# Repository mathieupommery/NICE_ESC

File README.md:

# NICE ESC

**A two-board, high-current three-phase inverter for BLDC/PMSM motor control and bidirectional power conversion.**

## Capabilities and key components

- **4S–16S Li-ion design range** or **84 V / 20S variant** with higher-voltage MOSFETs.
- **200 A peak phase-current design target**, with double-pulse switching tests extended to approximately **328 A** at a 40 V bus. Need a good cooling and test in continuous current.
- Hardware for **six-step control, FOC, Hall-based position feedback and active rectification**, depending on the firmware.
- all TOLT top side cooled mosfet to keep the case cost low we only have to cool down one isde of the inverter, also no need for aluminium or copper pcb.

| Function | Hardware |
|---|---|
| Controller | STM32G431CBU, complementary PWM and synchronized ADC acquisition |
| Power switches | 12 × IAUS300N10S5N015T, with two MOSFETs in parallel per switch |
| Gate drive | UCC27301A half-bridge drivers, bootstrap circuits and approximately 11 V gate supply |
| Current sensing | Shunts and INA241 amplifiers located on the power PCB |
| Signal conditioning | Switchable RC filters for current and voltage measurements |
| Auxiliary rails | LM5169 bus-to-11 V buck, LMR51625 11-to-5 V buck, separate 3.3 V digital and analog rails |
| Interconnects | M5 battery/phase terminals and locking JST-GH signal connectors |
| PCB stack-up | Four copper layers on the control board; two on the power board |

The published switching measurements were made at approximately **40 V**, not at the maximum intended battery voltage.

## V2 architecture

The two boards share a common electrical reference. Gate drivers, gate components and current amplifiers are kept close to the power devices, so the board-to-board connections carry logic-level PWM and amplified measurements rather than long gate loops or raw shunt signals.An effort has been put on the esd and overvoltage protection, each voltage rail has it's on esd protection as well as each connection.

## Assembly and mechanical integration

The control PCB sits above the power PCB. Top-side-cooled TOLT MOSFETs are mounted on the underside of the power board, providing access to their cooling surfaces. STEP models of both boards and the enclosure are included.

## TOLT MOSFET options

The baseline device is the **IAUS300N10S5N015T**, an OptiMOS 5 100 V TOLT MOSFET. Higher-voltage OptiMOS 6 devices offer a useful trade-off between voltage headroom and on-resistance:

| Device | Technology | VDS rating | Maximum RDS(on), VGS = 10 V | Role |
|---|---|---:|---:|---|
| [IAUS300N10S5N015T](https://www.infineon.com/part/IAUS300N10S5N015T) | OptiMOS 5 | 100 V | 1.5 mΩ | Baseline build |
| [IPTC017N12NM6](https://www.infineon.com/part/IPTC017N12NM6) | OptiMOS 6 | 120 V | 1.7 mΩ | Higher-voltage candidate |
| [IPTC020N13NM6](https://www.infineon.com/part/IPTC020N13NM6) | OptiMOS 6 | 135 V | 2.0 mΩ | Additional voltage headroom |

The 120 V option adds only 0.2 mΩ relative to the baseline.Also infineon will eventually create new optimos 8 mosfet in tolt wich can improve the choice.

## Double-pulse testing

A double-pulse test first builds current in an air-core inductor, then captures turn-off and the subsequent turn-on under load. The measurements below were taken at approximately **40 V bus voltage and 200 A inductor current**, using an approximately **8 µH** air-core load, all measurment are donne at 2.5Gsamples/s on tektronix MDO3034 scope with 1GHz probes.

At 200 A, the recorded drain-source peaks remain around **60 V on a 40 V bus**, leaving substantial headroom below the baseline MOSFET's 100 V rating. The extracted VDS transition times are approximately **101 ns at turn-on** and **33 ns at turn-off**. These are voltage-edge durations, not complete gate-command delays.

The test campaign was also pushed to approximately **328 A**, the current acquisition range limit, without a notable increase in the observed VDS peaks. The plots shown here are the **200 A acquisition**. These short-pulse results are encouraging for the commutation layout; sustained phase-current capability still depends on thermal validation.

The measured current is the inductor current, so the captures are used to assess overshoot and ringing rather than to claim precise Eon/Eoff measurements. [Raw acquisitions and the viewer](DOC_AND_SIMULATION/DPT_200A/) and the [LTspice test circuit](DOC_AND_SIMULATION/LTSPICE_SIMULATION_DPT/) are included.

## DC-link decoupling

The DC link combines bulk energy storage with local, low-inductance ceramic decoupling:

| Capacitor bank | Selection | Purpose |
|---|---|---|
| Bulk electrolytics | **4 × 820 µF / 100 V = 3280 µF** | Reduce the lower-frequency DC-link ripple and supply transient energy |
| Local MLCCs | **18 × 4.7 µF / 100 V, 2220 = 84.6 µF nominal** | Supply fast switching-current loops close to the half-bridges and limit parasitic-inductance overshoot |

For a first-order capacitive-ripple estimate, `ΔVpp ≈ Iphase,peak / (4 × fPWM × Cbulk)`. At **200 A and 20 kHz**, a 2 V ripple target gives **1250 µF minimum**; the selected 3280 µF gives approximately **0.76 V calculated capacitive ripple**. Actual ripple also depends on ESR/ESL, RMS current and temperature. The MLCC total is nominal: effective capacitance falls with DC bias. Placement and short commutation loops matter alongside the capacitance value.

## Repository

| Directory | Contents |
|---|---|
| [Control PCB](HARDWARE/V2/CONTROL_BOARD_V2/) | KiCad project, schematics, layout and local libraries |
| [Power PCB](HARDWARE/V2/POWER_BOARD_V2/) | KiCad project, schematics, layout and local libraries |
| [Board STEP models](HARDWARE/V2/3D/) | Mechanical board assemblies |
| [Enclosure](HARDWARE/INVERTER_CASE_3D/) | Top and bottom STEP models |
| [Documentation and simulation](DOC_AND_SIMULATION/) | DPT data, LTspice files and project media |

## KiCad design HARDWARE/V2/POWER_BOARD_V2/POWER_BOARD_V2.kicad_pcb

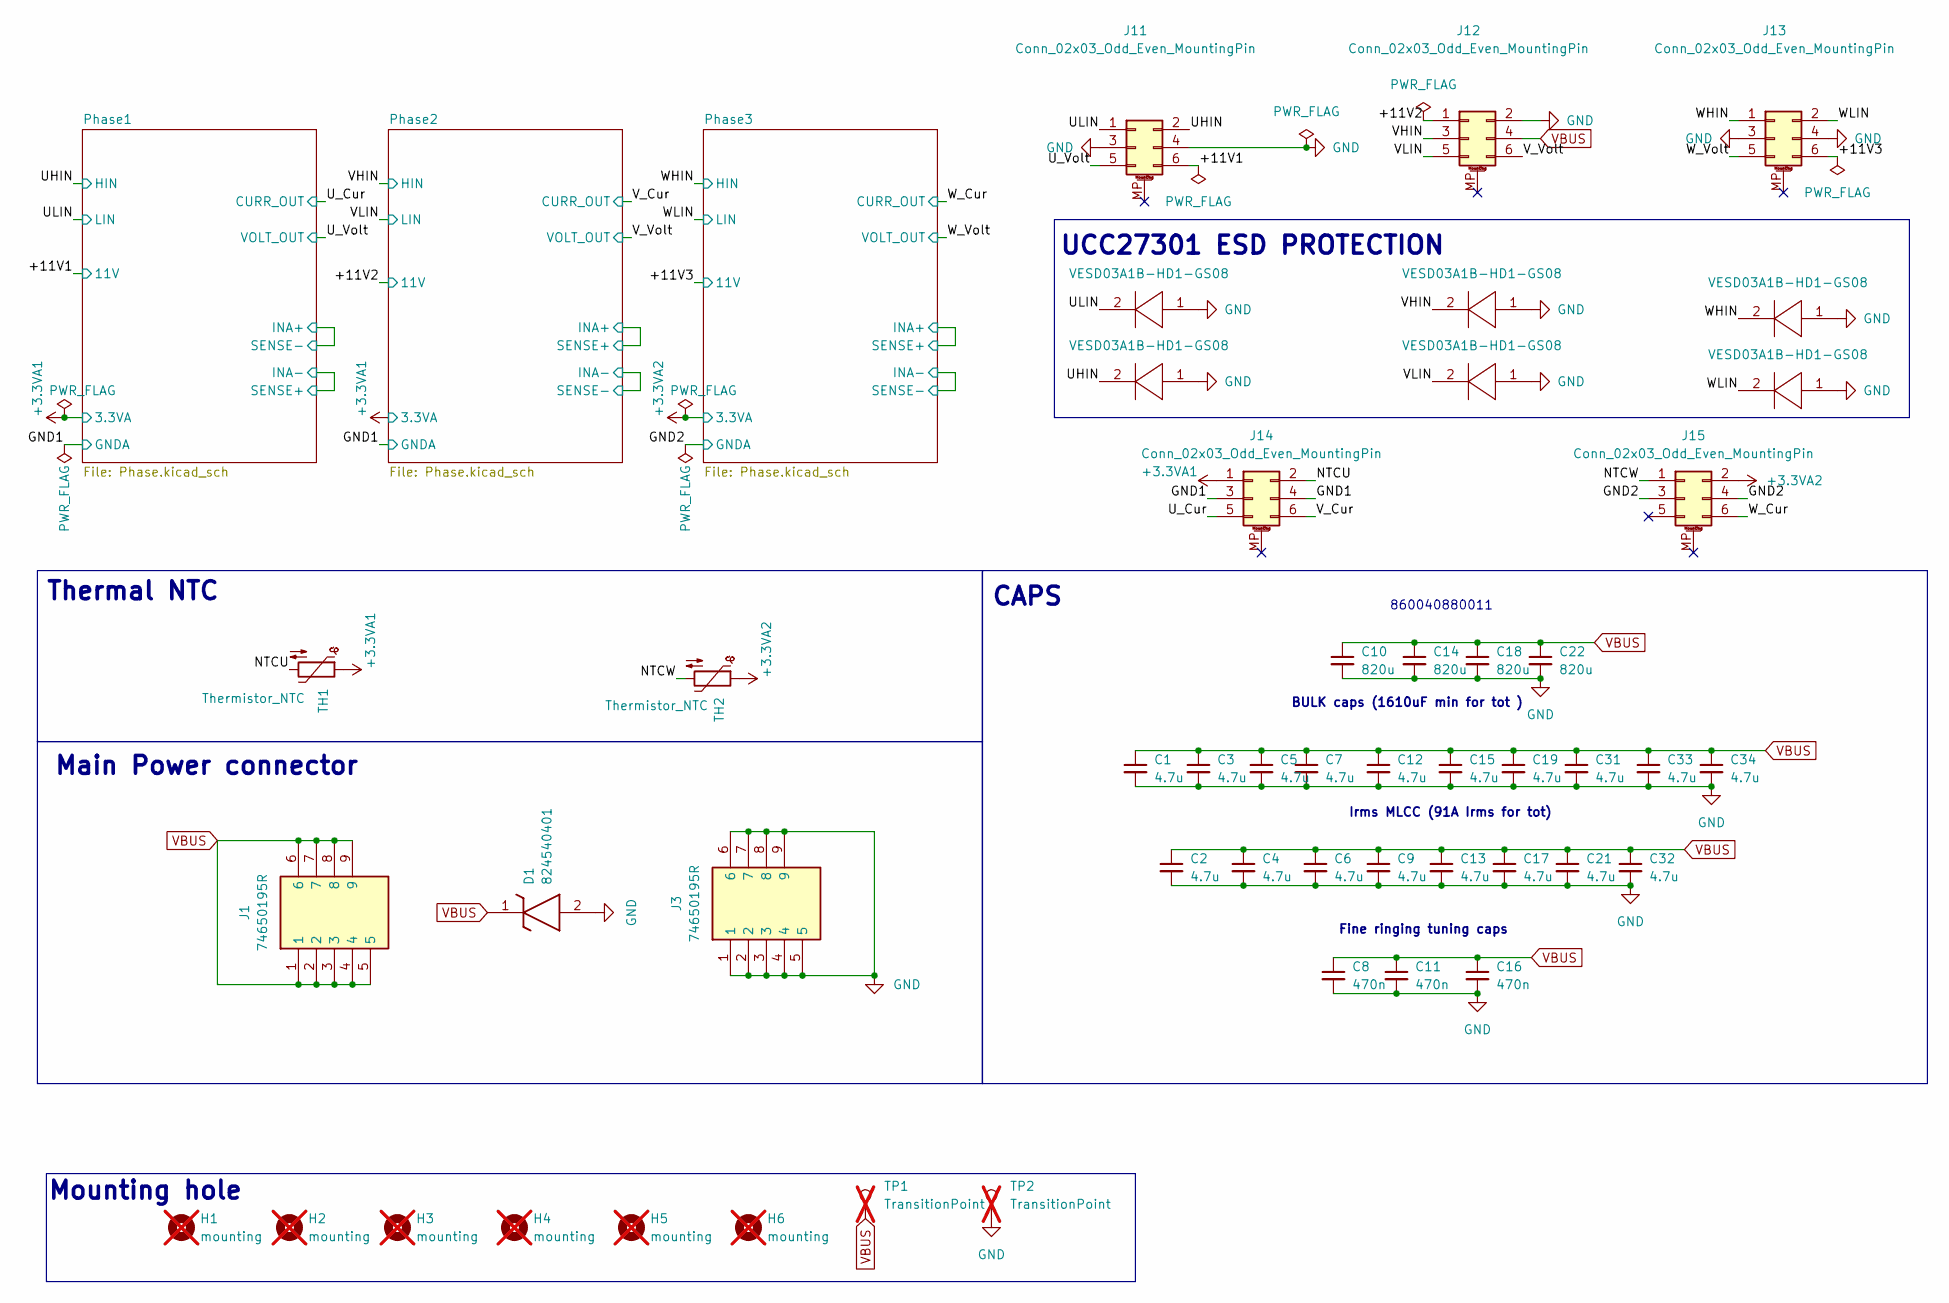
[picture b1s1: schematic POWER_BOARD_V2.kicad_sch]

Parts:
C1, C2, C3, C4, C5, C6, C7, C9, C12, C13, C15, C17, C19, C21, C31, C32, C33, C34: 4.7u; C_2220_5750Metric
C8, C11, C16: 470n; C_1206_3216Metric
C10, C14, C18, C22: 820u; CAPPRD750W82D1800H3300
D1: 824540401; DIOM7959X250N; Manufacturer_Part_Number 824540401; Mouser Part Number 710-824540401
D19, D20, D21, D22, D23, D24: VESD03A1B-HD1-GS08; VCUT0714AHD1G308; Manufacturer_Part_Number VESD03A1B-HD1-GS08; Mouser Part Number 78-VESD03A1B-HD1
H1, H2, H3, H4, H5, H6: mounting; MountingHole_3.2mm_M3_ISO7380; not fitted
J1, J3: 74650195R; 74651194R; Manufacturer_Part_Number 74650195R; Mouser Part Number 710-74650195R
J11, J12, J13, J14, J15: Conn_02x03_Odd_Even_MountingPin; pinheader_02x03_Custom
TH1, TH2: Thermistor_NTC; R_0402_1005Metric
TP1, TP2: TransitionPoint; bighole2mm; not fitted

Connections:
+3.3VA1: J14.1, TH1.1; also elsewhere on the board
+3.3VA2: J15.2, TH2.1; also elsewhere on the board
/+11V1: J11.6; also elsewhere on the board
/+11V2: J12.1; also elsewhere on the board
/+11V3: J13.6; also elsewhere on the board
/GND1: J14.3, J14.4; also elsewhere on the board
/GND2: J15.3, J15.4; also elsewhere on the board
/NTCU: J14.2, TH1.2
/NTCW: J15.1, TH2.2
/UHIN: D20.2, D20.4 (K_2), J11.2; also elsewhere on the board
/ULIN: D19.2, D19.4 (K_2), J11.1; also elsewhere on the board
/U_Cur: J14.5; also elsewhere on the board
/U_Volt: J11.5; also elsewhere on the board
/VHIN: D21.2, D21.4 (K_2), J12.3; also elsewhere on the board
/VLIN: D22.2, D22.4 (K_2), J12.5; also elsewhere on the board
/V_Cur: J14.6; also elsewhere on the board
/V_Volt: J12.6; also elsewhere on the board
/WHIN: D23.2, D23.4 (K_2), J13.1; also elsewhere on the board
/WLIN: D24.2, D24.4 (K_2), J13.2; also elsewhere on the board
/W_Cur: J15.6; also elsewhere on the board
/W_Volt: J13.5; also elsewhere on the board
GND: C1.2, C2.2, C3.2, C4.2, C5.2, C6.2, C7.2, C8.2, C9.2, C10.2, C11.2, C12.2, C13.2, C14.2, C15.2, C16.2, C17.2, C18.2, C19.2, C21.2, C22.2, C31.2, C32.2, C33.2, C34.2, D1.2 (A), D19.1, D19.3 (A_2), D20.1, D20.3 (A_2), D21.1, D21.3 (A_2), D22.1, D22.3 (A_2), D23.1, D23.3 (A_2), D24.1, D24.3 (A_2), J3.1, J3.2, J3.3, J3.4, J3.5, J3.6, J3.7, J3.8, J3.9, J11.3, J11.4, J12.2, J13.3, J13.4, TP2.1 (1_1); also elsewhere on the board
VBUS: C1.1, C2.1, C3.1, C4.1, C5.1, C6.1, C7.1, C8.1, C9.1, C10.1, C11.1, C12.1, C13.1, C14.1, C15.1, C16.1, C17.1, C18.1, C19.1, C21.1, C22.1, C31.1, C32.1, C33.1, C34.1, D1.1 (K), J1.1, J1.2, J1.3, J1.4, J1.5, J1.6, J1.7, J1.8, J1.9, J12.4, TP1.1 (1_1); also elsewhere on the board

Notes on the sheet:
CAPS
Main Power connector
Thermal NTC
Mounting hole
Irms MLCC (91A Irms for tot)
Fine ringing tuning caps
BULK caps (1610uF min for tot )
860040880011
UCC27301 ESD PROTECTION

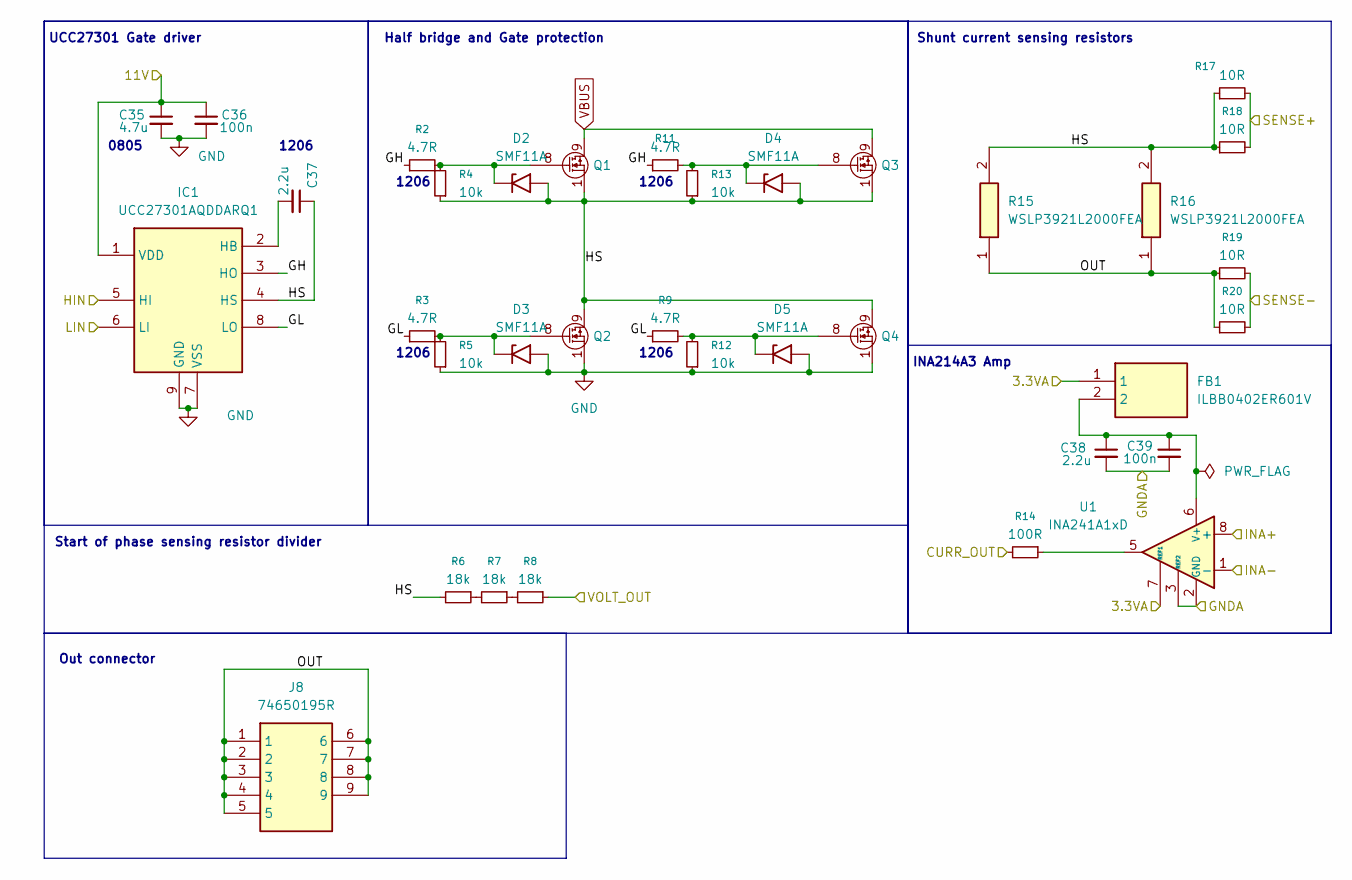
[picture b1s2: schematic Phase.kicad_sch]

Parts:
C35: 4.7u; C_0805_2012Metric
C36, C39: 100n; C_0402_1005Metric
C37: 2.2u; C_1206_3216Metric
C38: 2.2u; C_0402_1005Metric
D2, D3, D4, D5: SMF11A; SMF_Custom
FB1: ILBB0402ER601V; BEADC1005X60N; Manufacturer_Part_Number ILBB0402ER601V; Mouser Part Number 70-ILBB0402ER601V
IC1: UCC27301AQDDARQ1; SOIC127P600X170-9N; Manufacturer_Part_Number UCC27301AQDDARQ1; Mouser Part Number 595-UCC27301AQDDARQ1
J8: 74650195R; 74651194R; Manufacturer_Part_Number 74650195R; Mouser Part Number 710-74650195R
Q1, Q2, Q3, Q4: IAUS300N10S5N015TATMA1; SOP120P1500X235-16N; Manufacturer_Part_Number IAUS300N10S5N015TATMA1; Mouser Part Number 726-US300N10S5N015T1
R2, R3, R9, R11: 4.7R; R_1206_3216Metric
R4, R5, R12, R13: 10k; R_0402_1005Metric
R6, R7, R8: 18k; R_0402_1005Metric
R14: 100R; R_0402_1005Metric
R15, R16: WSLP3921L2000FEA; RESC10052X69N; Manufacturer_Part_Number WSLP3921L2000FEA; Mouser Part Number 71-WSLP3921L2000FEA
R17, R18, R19, R20: 10R; R_0402_1005Metric
U1: INA241A1xD; SOIC-8_3.9x4.9mm_P1.27mm

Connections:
+3.3VA1: FB1.1, U1.7 (REF1); also elsewhere on the board
/+11V1: C35.1, C36.1, IC1.1 (VDD); also elsewhere on the board
/GND1: C38.2, C39.2, U1.2 (GND), U1.3 (REF2), U1.4 (GND); also elsewhere on the board
/Phase1/GH: IC1.3 (HO), R2.1, R11.1
/Phase1/GL: IC1.8 (LO), R3.1, R9.1
/Phase1/HS: C37.1, D2.2 (A2), D4.2 (A2), IC1.4 (HS), Q1.1, Q1.2 (S_2), Q1.3 (S_3), Q1.4 (S_4), Q1.5 (S_5), Q1.6 (S_6), Q1.7 (S_7), Q2.9, Q2.10 (D_2), Q2.11 (D_3), Q2.12 (D_4), Q2.13 (D_5), Q2.14 (D_6), Q2.15 (D_7), Q2.16 (D_8), Q3.1, Q3.2 (S_2), Q3.3 (S_3), Q3.4 (S_4), Q3.5 (S_5), Q3.6 (S_6), Q3.7 (S_7), Q4.9, Q4.10 (D_2), Q4.11 (D_3), Q4.12 (D_4), Q4.13 (D_5), Q4.14 (D_6), Q4.15 (D_7), Q4.16 (D_8), R4.1, R6.2, R13.1, R15.2, R16.2, R17.1, R18.1
/Phase1/INA+: R19.2, R20.2, U1.8 (+)
/Phase1/INA-: R17.2, R18.2, U1.1 (-)
/Phase1/OUT: J8.1, J8.2, J8.3, J8.4, J8.5, J8.6, J8.7, J8.8, J8.9, R15.1, R16.1, R19.1, R20.1
/UHIN: IC1.5 (HI); also elsewhere on the board
/ULIN: IC1.6 (LI); also elsewhere on the board
/U_Cur: R14.2; also elsewhere on the board
/U_Volt: R8.1; also elsewhere on the board
GND: C35.2, C36.2, D3.2 (A2), D5.2 (A2), IC1.7 (VSS), IC1.9 (GND), Q2.1, Q2.2 (S_2), Q2.3 (S_3), Q2.4 (S_4), Q2.5 (S_5), Q2.6 (S_6), Q2.7 (S_7), Q4.1, Q4.2 (S_2), Q4.3 (S_3), Q4.4 (S_4), Q4.5 (S_5), Q4.6 (S_6), Q4.7 (S_7), R5.1, R12.1; also elsewhere on the board
unnamed: D2.1 (A1), Q1.8, R2.2, R4.2
unnamed: D3.1 (A1), Q2.8, R3.2, R5.2
unnamed: D4.1 (A1), Q3.8, R11.2, R13.2
unnamed: D5.1 (A1), Q4.8, R9.2, R12.2
unnamed: C37.2, IC1.2 (HB)
unnamed: R6.1, R7.2
unnamed: R7.1, R8.2
unnamed: R14.1, U1.5
unnamed: C38.1, C39.1, FB1.2, U1.6 (V+)
VBUS: Q1.9, Q1.10 (D_2), Q1.11 (D_3), Q1.12 (D_4), Q1.13 (D_5), Q1.14 (D_6), Q1.15 (D_7), Q1.16 (D_8), Q3.9, Q3.10 (D_2), Q3.11 (D_3), Q3.12 (D_4), Q3.13 (D_5), Q3.14 (D_6), Q3.15 (D_7), Q3.16 (D_8); also elsewhere on the board

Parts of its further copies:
C40, C45: 4.7u; C_0805_2012Metric
C41, C44, C46, C49: 100n; C_0402_1005Metric
C42, C47: 2.2u; C_1206_3216Metric
C43, C48: 2.2u; C_0402_1005Metric
D6, D7, D8, D9, D10, D11, D12, D13: SMF11A; SMF_Custom
FB2, FB3: ILBB0402ER601V; BEADC1005X60N; Manufacturer_Part_Number ILBB0402ER601V; Mouser Part Number 70-ILBB0402ER601V
IC2, IC3: UCC27301AQDDARQ1; SOIC127P600X170-9N; Manufacturer_Part_Number UCC27301AQDDARQ1; Mouser Part Number 595-UCC27301AQDDARQ1
J9, J10: 74650195R; 74651194R; Manufacturer_Part_Number 74650195R; Mouser Part Number 710-74650195R
Q5, Q6, Q7, Q8, Q9, Q10, Q11, Q12: IAUS300N10S5N015TATMA1; SOP120P1500X235-16N; Manufacturer_Part_Number IAUS300N10S5N015TATMA1; Mouser Part Number 726-US300N10S5N015T1
R21, R22, R28, R30, R40, R41, R47, R49: 4.7R; R_1206_3216Metric
R23, R24, R31, R32, R42, R43, R50, R51: 10k; R_0402_1005Metric
R25, R26, R27, R44, R45, R46: 18k; R_0402_1005Metric
R33, R52: 100R; R_0402_1005Metric
R34, R35, R53, R54: WSLP3921L2000FEA; RESC10052X69N; Manufacturer_Part_Number WSLP3921L2000FEA; Mouser Part Number 71-WSLP3921L2000FEA
R36, R37, R38, R39, R55, R56, R57, R58: 10R; R_0402_1005Metric
U2, U3: INA241A1xD; SOIC-8_3.9x4.9mm_P1.27mm

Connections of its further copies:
+3.3VA1: FB2.1, U2.7 (REF1); also elsewhere on the board
+3.3VA2: FB3.1, U3.7 (REF1); also elsewhere on the board
/+11V2: C40.1, C41.1, IC2.1 (VDD); also elsewhere on the board
/+11V3: C45.1, C46.1, IC3.1 (VDD); also elsewhere on the board
/GND1: C43.2, C44.2, U2.2 (GND), U2.3 (REF2), U2.4 (GND); also elsewhere on the board
/GND2: C48.2, C49.2, U3.2 (GND), U3.3 (REF2), U3.4 (GND); also elsewhere on the board
/Phase2/GH: IC2.3 (HO), R21.1, R30.1
/Phase2/GL: IC2.8 (LO), R22.1, R28.1
/Phase2/HS: C42.1, D6.2 (A2), D8.2 (A2), IC2.4 (HS), Q5.1, Q5.2 (S_2), Q5.3 (S_3), Q5.4 (S_4), Q5.5 (S_5), Q5.6 (S_6), Q5.7 (S_7), Q6.9, Q6.10 (D_2), Q6.11 (D_3), Q6.12 (D_4), Q6.13 (D_5), Q6.14 (D_6), Q6.15 (D_7), Q6.16 (D_8), Q7.1, Q7.2 (S_2), Q7.3 (S_3), Q7.4 (S_4), Q7.5 (S_5), Q7.6 (S_6), Q7.7 (S_7), Q8.9, Q8.10 (D_2), Q8.11 (D_3), Q8.12 (D_4), Q8.13 (D_5), Q8.14 (D_6), Q8.15 (D_7), Q8.16 (D_8), R23.1, R25.2, R32.1, R34.2, R35.2, R36.1, R37.1
/Phase2/INA+: R36.2, R37.2, U2.8 (+)
/Phase2/INA-: R38.2, R39.2, U2.1 (-)
/Phase2/OUT: J9.1, J9.2, J9.3, J9.4, J9.5, J9.6, J9.7, J9.8, J9.9, R34.1, R35.1, R38.1, R39.1
/Phase3/GH: IC3.3 (HO), R40.1, R49.1
/Phase3/GL: IC3.8 (LO), R41.1, R47.1
/Phase3/HS: C47.1, D10.2 (A2), D12.2 (A2), IC3.4 (HS), Q9.1, Q9.2 (S_2), Q9.3 (S_3), Q9.4 (S_4), Q9.5 (S_5), Q9.6 (S_6), Q9.7 (S_7), Q10.9, Q10.10 (D_2), Q10.11 (D_3), Q10.12 (D_4), Q10.13 (D_5), Q10.14 (D_6), Q10.15 (D_7), Q10.16 (D_8), Q11.1, Q11.2 (S_2), Q11.3 (S_3), Q11.4 (S_4), Q11.5 (S_5), Q11.6 (S_6), Q11.7 (S_7), Q12.9, Q12.10 (D_2), Q12.11 (D_3), Q12.12 (D_4), Q12.13 (D_5), Q12.14 (D_6), Q12.15 (D_7), Q12.16 (D_8), R42.1, R44.2, R51.1, R53.2, R54.2, R55.1, R56.1
/Phase3/INA+: R55.2, R56.2, U3.8 (+)
/Phase3/INA-: R57.2, R58.2, U3.1 (-)
/Phase3/OUT: J10.1, J10.2, J10.3, J10.4, J10.5, J10.6, J10.7, J10.8, J10.9, R53.1, R54.1, R57.1, R58.1
/VHIN: IC2.5 (HI); also elsewhere on the board
/VLIN: IC2.6 (LI); also elsewhere on the board
/V_Cur: R33.2; also elsewhere on the board
/V_Volt: R27.1; also elsewhere on the board
/WHIN: IC3.5 (HI); also elsewhere on the board
/WLIN: IC3.6 (LI); also elsewhere on the board
/W_Cur: R52.2; also elsewhere on the board
/W_Volt: R46.1; also elsewhere on the board
GND: C40.2, C41.2, C45.2, C46.2, D7.2 (A2), D9.2 (A2), D11.2 (A2), D13.2 (A2), IC2.7 (VSS), IC2.9 (GND), IC3.7 (VSS), IC3.9 (GND), Q6.1, Q6.2 (S_2), Q6.3 (S_3), Q6.4 (S_4), Q6.5 (S_5), Q6.6 (S_6), Q6.7 (S_7), Q8.1, Q8.2 (S_2), Q8.3 (S_3), Q8.4 (S_4), Q8.5 (S_5), Q8.6 (S_6), Q8.7 (S_7), Q10.1, Q10.2 (S_2), Q10.3 (S_3), Q10.4 (S_4), Q10.5 (S_5), Q10.6 (S_6), Q10.7 (S_7), Q12.1, Q12.2 (S_2), Q12.3 (S_3), Q12.4 (S_4), Q12.5 (S_5), Q12.6 (S_6), Q12.7 (S_7), R24.1, R31.1, R43.1, R50.1; also elsewhere on the board
unnamed: D6.1 (A1), Q5.8, R21.2, R23.2
unnamed: D7.1 (A1), Q6.8, R22.2, R24.2
unnamed: D8.1 (A1), Q7.8, R30.2, R32.2
unnamed: D9.1 (A1), Q8.8, R28.2, R31.2
unnamed: D10.1 (A1), Q9.8, R40.2, R42.2
unnamed: D11.1 (A1), Q10.8, R41.2, R43.2
unnamed: D12.1 (A1), Q11.8, R49.2, R51.2
unnamed: D13.1 (A1), Q12.8, R47.2, R50.2
unnamed: C42.2, IC2.2 (HB)
unnamed: C47.2, IC3.2 (HB)
unnamed: R25.1, R26.2
unnamed: R26.1, R27.2
unnamed: R33.1, U2.5
unnamed: R44.1, R45.2
unnamed: R45.1, R46.2
unnamed: R52.1, U3.5
unnamed: C43.1, C44.1, FB2.2, U2.6 (V+)
unnamed: C48.1, C49.1, FB3.2, U3.6 (V+)
VBUS: Q5.9, Q5.10 (D_2), Q5.11 (D_3), Q5.12 (D_4), Q5.13 (D_5), Q5.14 (D_6), Q5.15 (D_7), Q5.16 (D_8), Q7.9, Q7.10 (D_2), Q7.11 (D_3), Q7.12 (D_4), Q7.13 (D_5), Q7.14 (D_6), Q7.15 (D_7), Q7.16 (D_8), Q9.9, Q9.10 (D_2), Q9.11 (D_3), Q9.12 (D_4), Q9.13 (D_5), Q9.14 (D_6), Q9.15 (D_7), Q9.16 (D_8), Q11.9, Q11.10 (D_2), Q11.11 (D_3), Q11.12 (D_4), Q11.13 (D_5), Q11.14 (D_6), Q11.15 (D_7), Q11.16 (D_8); also elsewhere on the board

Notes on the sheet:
1206
Shunt current sensing resistors
0805
Half bridge and Gate protection
Start of phase sensing resistor divider
UCC27301 Gate driver
Out connector
INA214A3 Amp

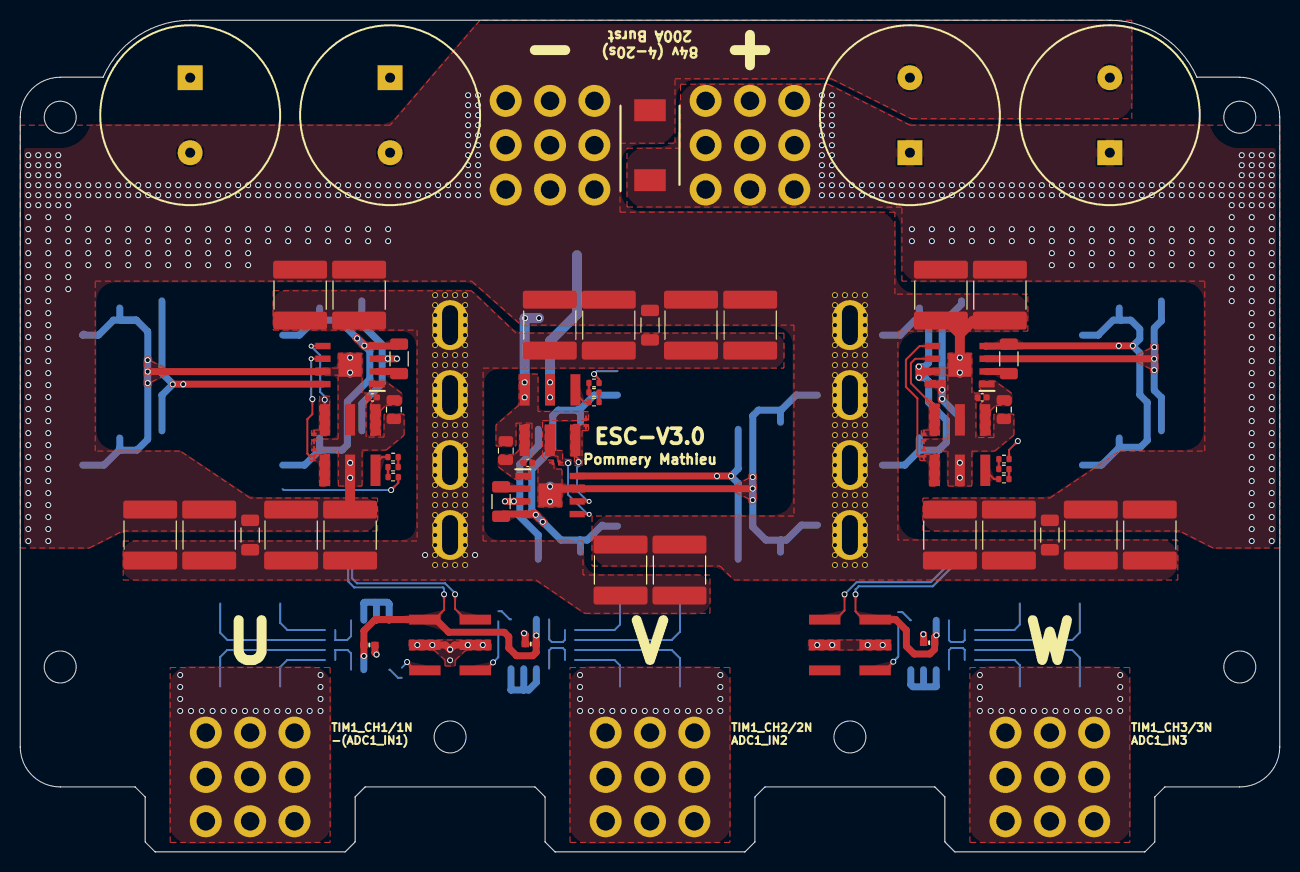
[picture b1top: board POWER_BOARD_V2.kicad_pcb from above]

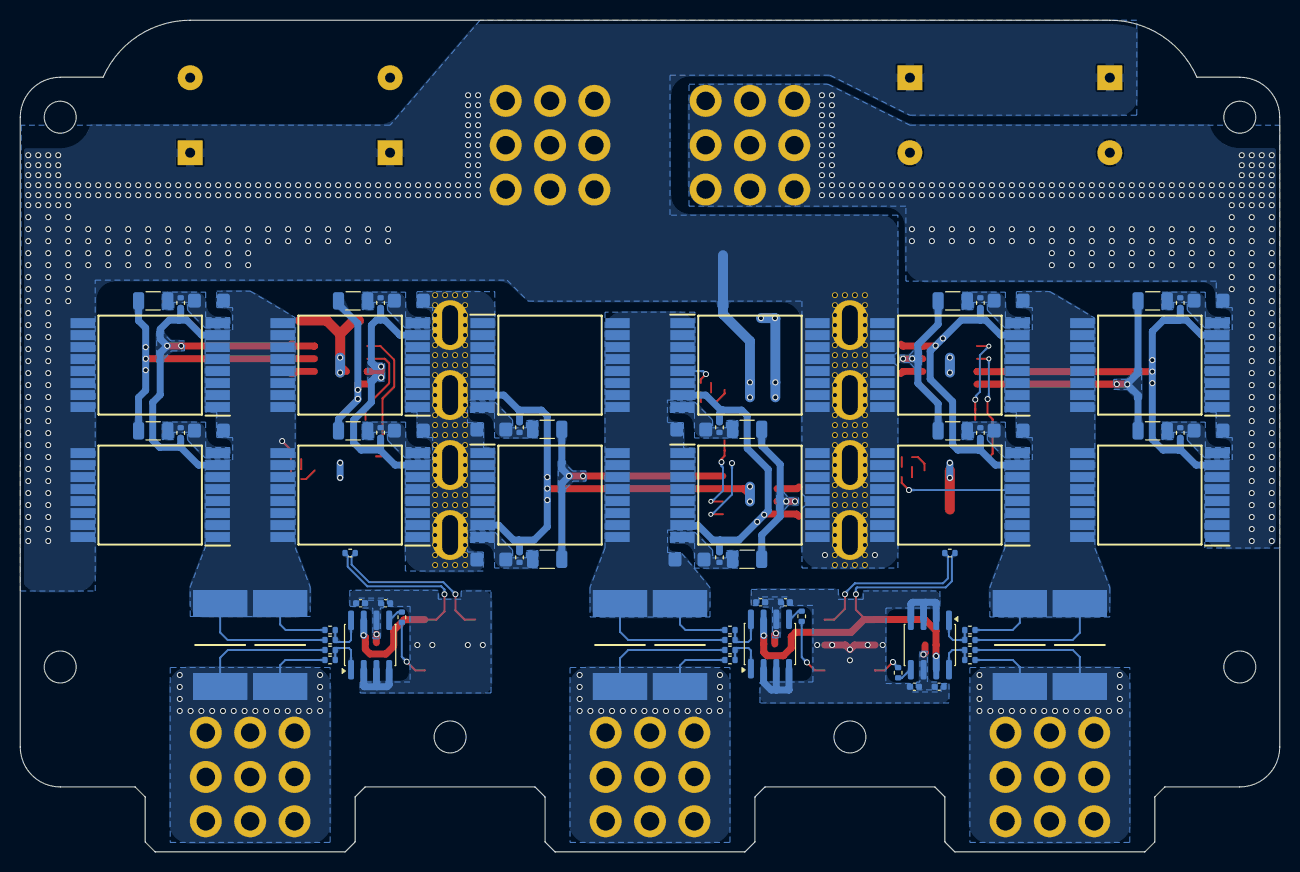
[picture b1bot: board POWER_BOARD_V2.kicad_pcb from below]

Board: 2 copper layers, 126.0 x 83.2 mm, 154 parts (80 on the bottom side), 68 nets.

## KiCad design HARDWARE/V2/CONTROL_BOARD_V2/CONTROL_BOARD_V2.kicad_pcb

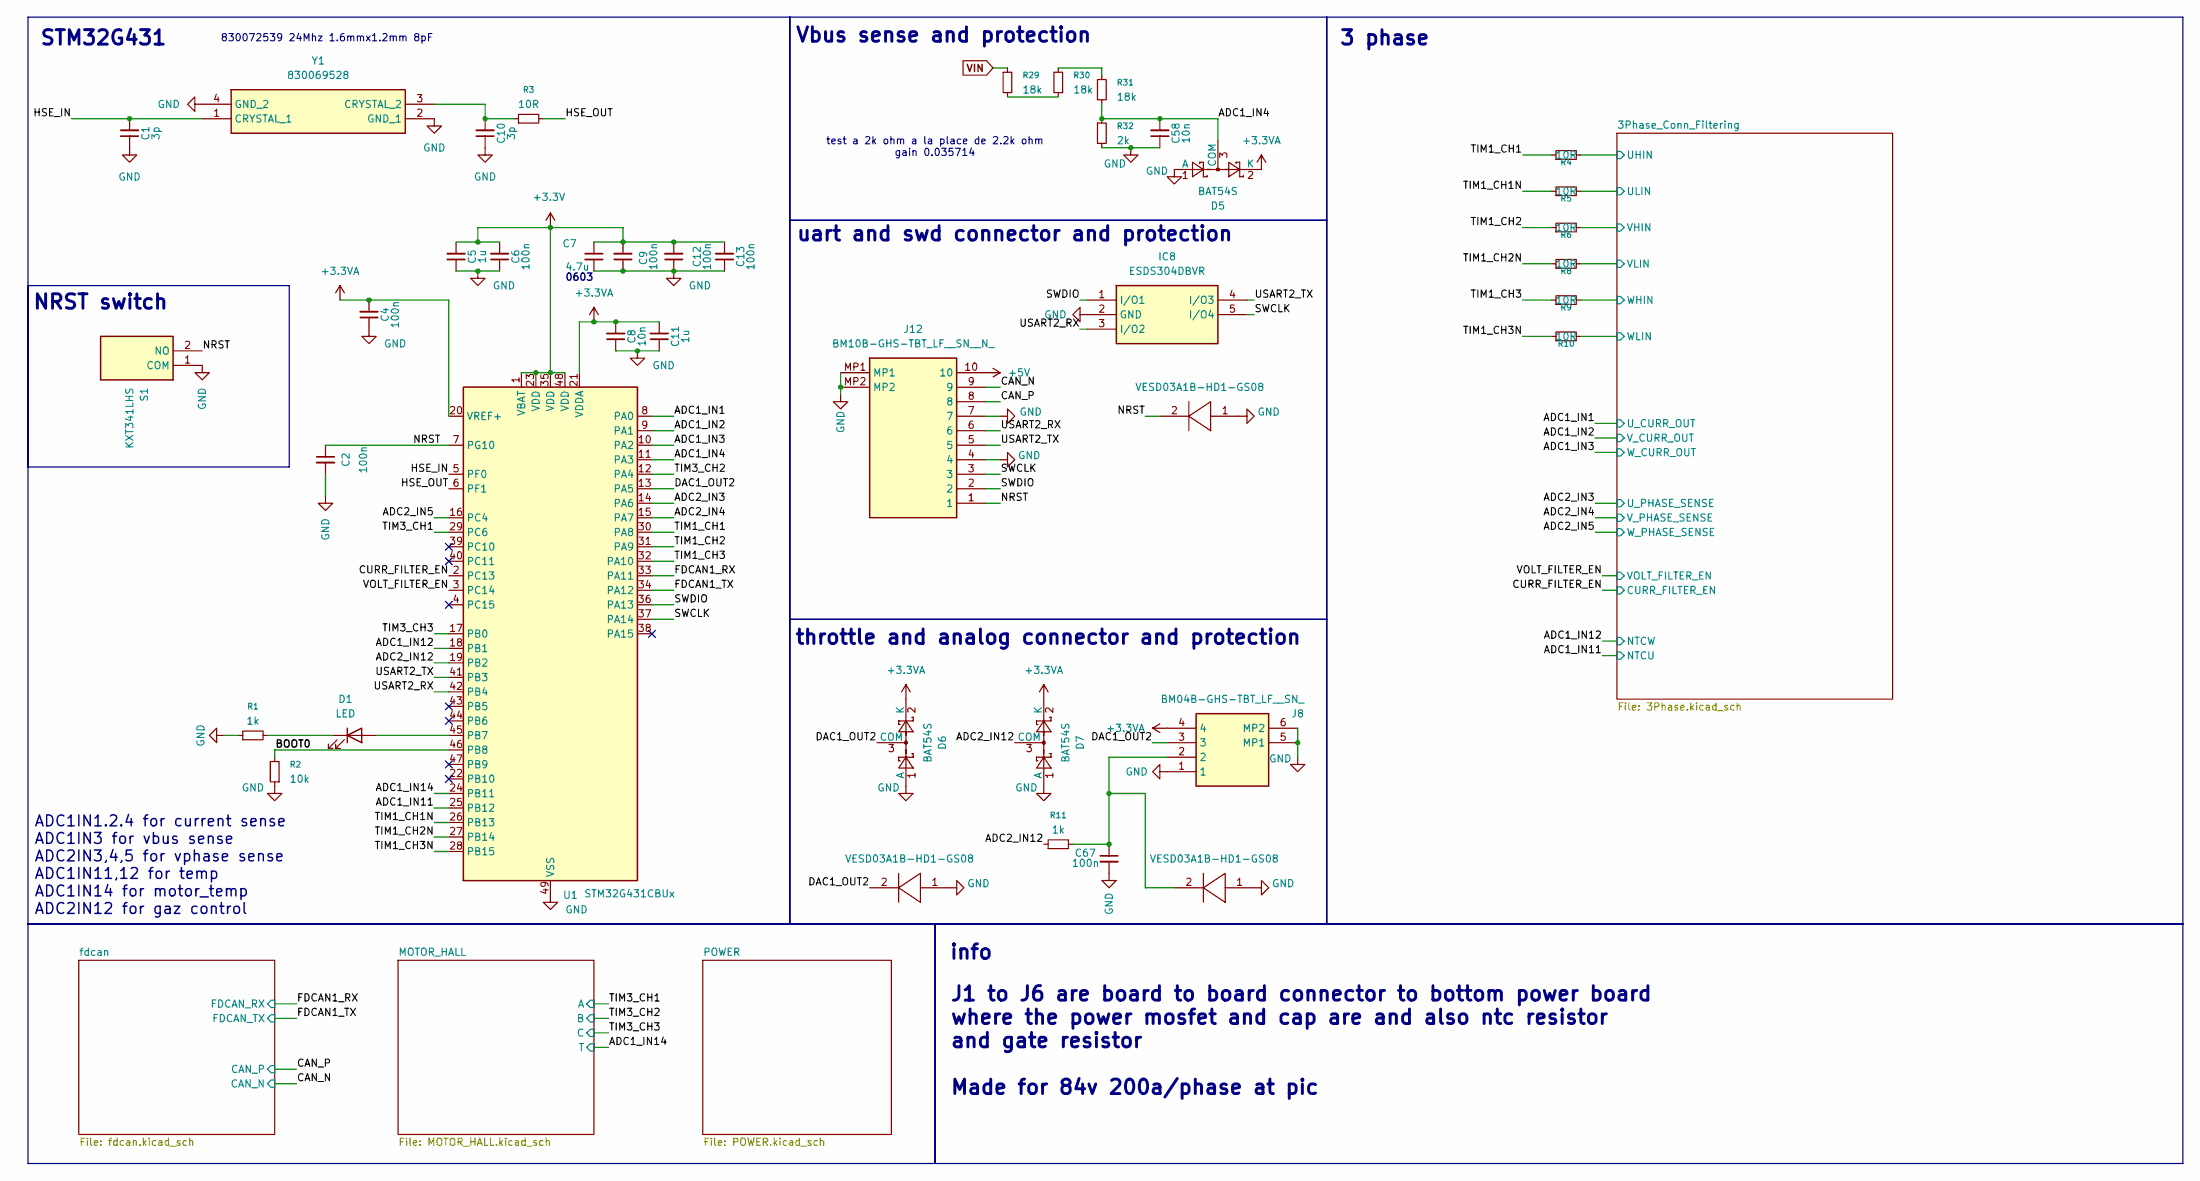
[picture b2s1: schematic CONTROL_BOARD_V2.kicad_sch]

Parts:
C1, C10: 3p; C_0402_1005Metric
C2, C4, C6, C9, C12, C13, C67: 100n; C_0402_1005Metric
C5, C11: 1u; C_0402_1005Metric
C7: 4.7u; C_0603_1608Metric
C8, C58: 10n; C_0402_1005Metric
D1: LED; LED_0402_1005Metric
D5, D6, D7: BAT54S; SOT-23
D18, D19, D21: VESD03A1B-HD1-GS08; VCUT0714AHD1G308; Manufacturer_Part_Number VESD03A1B-HD1-GS08; Mouser Part Number 78-VESD03A1B-HD1
IC8: ESDS304DBVR; SOT95P280X145-5N; Manufacturer_Part_Number ESDS304DBVR; Mouser Part Number 595-ESDS304DBVR
J8: BM04B-GHS-TBT_LF__SN_; BM04BGHSTBTLFSN; Manufacturer_Part_Number BM04B-GHS-TBT(LF)(SN); Mouser Part Number 306-BM04BGHSTBTLFSNN
J12: BM10B-GHS-TBT_LF__SN__N_; BM10BGHSTBTLFSNN; Manufacturer_Part_Number BM10B-GHS-TBT(LF)(SN)(N)
R1, R11: 1k; R_0402_1005Metric
R2: 10k; R_0402_1005Metric
R3, R4, R5, R6, R8, R9, R10: 10R; R_0402_1005Metric
R29, R30, R31: 18k; R_0402_1005Metric
R32: 2k; R_0402_1005Metric
S1: KXT341LHS; Manufacturer_Part_Number KXT341LHS; Mouser Part Number 611-KXT341LHS
U1: STM32G431CBUx; QFN-48-1EP_7x7mm_P0.5mm_EP5.6x5.6mm
Y1: 830069528; Manufacturer_Part_Number 830069528; Mouser Part Number 710-830069528

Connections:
+3.3V: C5.2, C6.2, C7.1, C9.2, C12.2, C13.2, U1.1 (VBAT), U1.23 (VDD), U1.35 (VDD), U1.48 (VDD); also elsewhere on the board
+3.3VA: C4.2, C8.2, C11.2, D5.2 (K), D6.2 (K), D7.2 (K), J8.4, U1.20 (VREF+), U1.21 (VDDA); also elsewhere on the board
+5V: J12.10; also elsewhere on the board
/3Phase_Conn_Filtering/UHIN: R4.2; also elsewhere on the board
/3Phase_Conn_Filtering/ULIN: R5.2; also elsewhere on the board
/3Phase_Conn_Filtering/VHIN: R6.2; also elsewhere on the board
/3Phase_Conn_Filtering/VLIN: R8.2; also elsewhere on the board
/3Phase_Conn_Filtering/WHIN: R9.2; also elsewhere on the board
/3Phase_Conn_Filtering/WLIN: R10.2; also elsewhere on the board
/ADC1_IN1: U1.8 (PA0); also elsewhere on the board
/ADC1_IN2: U1.9 (PA1); also elsewhere on the board
/ADC1_IN3: U1.10 (PA2); also elsewhere on the board
/ADC1_IN4: C58.2, D5.3 (COM), R31.2, R32.1, U1.11 (PA3)
/ADC1_IN11: U1.25 (PB12); also elsewhere on the board
/ADC1_IN12: U1.18 (PB1); also elsewhere on the board
/ADC1_IN14: U1.24 (PB11); also elsewhere on the board
/ADC2_IN3: U1.14 (PA6); also elsewhere on the board
/ADC2_IN4: U1.15 (PA7); also elsewhere on the board
/ADC2_IN5: U1.16 (PC4); also elsewhere on the board
/ADC2_IN12: D7.3 (COM), R11.1, U1.19 (PB2)
/BOOT0: R2.2, U1.46 (PB8)
/CAN_N: J12.9; also elsewhere on the board
/CAN_P: J12.8; also elsewhere on the board
/CURR_FILTER_EN: U1.2 (PC13); also elsewhere on the board
/DAC1_OUT2: D6.3 (COM), D21.2, D21.4 (K_2), J8.3, U1.13 (PA5)
/FDCAN1_RX: U1.33 (PA11); also elsewhere on the board
/FDCAN1_TX: U1.34 (PA12); also elsewhere on the board
/HSE_IN: C1.2, U1.5 (PF0), Y1.1 (CRYSTAL_1)
/HSE_OUT: R3.2, U1.6 (PF1)
/NRST: C2.1, D18.2, D18.4 (K_2), J12.1, S1.2 (NO), U1.7 (PG10)
/SWCLK: IC8.5 (I/O4), J12.3, U1.37 (PA14)
/SWDIO: IC8.1 (I/O1), J12.2, U1.36 (PA13)
/TIM1_CH1: R4.1, U1.30 (PA8)
/TIM1_CH1N: R5.1, U1.26 (PB13)
/TIM1_CH2: R6.1, U1.31 (PA9)
/TIM1_CH2N: R8.1, U1.27 (PB14)
/TIM1_CH3: R9.1, U1.32 (PA10)
/TIM1_CH3N: R10.1, U1.28 (PB15)
/TIM3_CH1: U1.29 (PC6); also elsewhere on the board
/TIM3_CH2: U1.12 (PA4); also elsewhere on the board
/TIM3_CH3: U1.17 (PB0); also elsewhere on the board
/USART2_RX: IC8.3 (I/O2), J12.6, U1.42 (PB4)
/USART2_TX: IC8.4 (I/O3), J12.5, U1.41 (PB3)
/VOLT_FILTER_EN: U1.3 (PC14); also elsewhere on the board
GND: C1.1, C2.2, C4.1, C5.1, C6.1, C7.2, C8.1, C9.1, C10.1, C11.1, C12.1, C13.1, C58.1, C67.2, D5.1 (A), D6.1 (A), D7.1 (A), D18.1, D18.3 (A_2), D19.1, D19.3 (A_2), D21.1, D21.3 (A_2), IC8.2 (GND), J8.1, J8.5 (MP1), J8.6 (MP2), J12.4, J12.7, J12.MP1, J12.MP2, R1.1, R2.1, R32.2, S1.1 (COM), U1.49 (VSS), Y1.2 (GND_1), Y1.4 (GND_2); also elsewhere on the board
unnamed: D1.2 (A), U1.45 (PB7)
unnamed: D1.1 (K), R1.2
unnamed: C67.1, D19.2, D19.4 (K_2), J8.2, R11.2
unnamed: R29.2, R30.1
unnamed: R30.2, R31.1
unnamed: C10.2, R3.1, Y1.3 (CRYSTAL_2)
VIN: R29.1; also elsewhere on the board

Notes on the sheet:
3 phase
Vbus sense and protection
info
NRST switch
0603
test a 2k ohm a la place de 2.2k ohm gain 0.035714
throttle and analog connector and protection
STM32G431
ADC1IN1.2.4 for current sense ADC1IN3 for vbus sense ADC2IN3,4,5 for vphase sense ADC1IN11,12 for temp ADC1IN14 for motor_temp ADC2IN12 for gaz control
J1 to J6 are board to board connector to bottom power board where the power mosfet and cap are and also ntc resistor and gate resistor Made for 84v 200a/phase at pic
uart and swd connector and protection
830072539 24Mhz 1.6mmx1.2mm 8pF
